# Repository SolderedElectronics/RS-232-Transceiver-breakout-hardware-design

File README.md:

# RS-232 Transceiver breakout Hardware Design

## About the Product

|  |
| :----------------------------------------------------------: |
| [Buy RS-232 Transceiver breakout](https://www.solde.red/333067) |

The RS-232 is a standard and very popular protocol for communication between two devices. It is a full-duplex protocol which means it can receive and send data at the same time, and data is sent at voltages from + 3V to + 15V for a digital “one” and from -3V to -15V for digital “zero”. This provides a more secure environment for data transmission which is resistant to noise or interference, which is why the RS-232 is often used in industry. This module converts serial communication to RS232.

---

## Repository Contents

This repository contains all design files for RS-232 Transceiver breakout, organized as follows:

- **`CAD` folder**: Contains KiCAD design files, including:
  - Schematics
  - PCB layout
  - Panel PCB layout
  - Source 3D files in Fusion360, if any
  - All files are sorted by version with a detailed change log.
- **`OUTPUTS` folder**: Includes all production-ready files, such as:
  - Bill of Materials (BOM) and interactive BOM (iBOM)
  - PDF versions of schematics
  - 3D `.step` file of the board
  - 3D-printable models
  - Gerber files for PCB manufacturing
  - Image of the pinout of the board
  - Product image
  - Compliance, legal and generic sales documents

Refer to the `Change Log` in the CAD folder for details about updates between versions.

---

## Learn More About the Product

Beyond the repository, explore the following resources:

### Soldered Verify

The **Soldered Verify** system ensures every board you purchase from Soldered is fully functional. It also provides access to exclusive test data for your product. To get started, find the unique Soldered Verify ID on your product's packaging and enter the ID on the [Soldered Verify page](https://soldered.com/verify/) to access test results and additional product details.

### Soldered Community

Soldered Community is your go-to place for technical support. Our engineers track and answer all questions posted there, and it’s a great space for the maker community. Get answers to your questions and solutions for your challenges at [Soldered Community](https://soldered.com/community).

### solde.red

solde.red is an ultimate URL shortener and information hub. Access it by typing solde.red/ followed by your product SKU, e.g., [solde.red/333000](https://solde.red/333000), to find getting-started guides, datasheets, open-source hardware and software files, certifications, images, pinouts, and more. Read more about the shortener [here](https://solde.red/info/).

---

## Contributing

Contributions are welcome! Here’s how you can get involved:

- Submit pull requests to enhance the design or fix issues.
- Report bugs or problems by opening an issue.

We encourage community collaboration to make this product even better.

---

## About Soldered

[Soldered for Makers](https://soldered.com) specializes in designing and manufacturing electronic products tailored for enthusiasts, ranging from hobbyists to professionals. Our portfolio includes electronic boards, sensors, and actuators that are widely utilized in fields such as microelectronics, mechatronics, robotics, programming, and IoT. Every product we offer is designed in-house and built upon open-source hardware and software platforms. Proudly certified and manufactured within the European Union, our catalog likely includes the product you need for your project.

We complement these products with comprehensive tutorials and manuals, product descriptions, schematics, programming codes, and project examples. Our round-the-clock [customer and technical support](https://soldered.com/community) is available for all our products, irrespective of the sales channel. Soldered’s success and services reflect our maker community’s unwavering [trust](https://www.trustpilot.com/review/soldered.com), for which we are deeply grateful. Join our community and create using Soldered products.

---

## License

All Soldered open-source hardware (OSH) is under The TAPR Open Hardware License. Read more in the LICENSE file located in this repository.

**Disclaimer:**

No warranty - all designs in this repository are distributed in the hope that they will be useful, but without any warranty. They are provided "AS IS", therefore without warranty of any kind, either expressed or implied. The entire quality and performance of what you do with the contents of this repository are your responsibility. In no event Soldered Electronics will be liable for your damages, or losses, including any general, special, incidental, or consequential damage arising out of the use or inability to use the contents of this repository. 

---

## Have fun!

Thank you for your support from your fellow makers at Soldered Electronics.

Happy Making!

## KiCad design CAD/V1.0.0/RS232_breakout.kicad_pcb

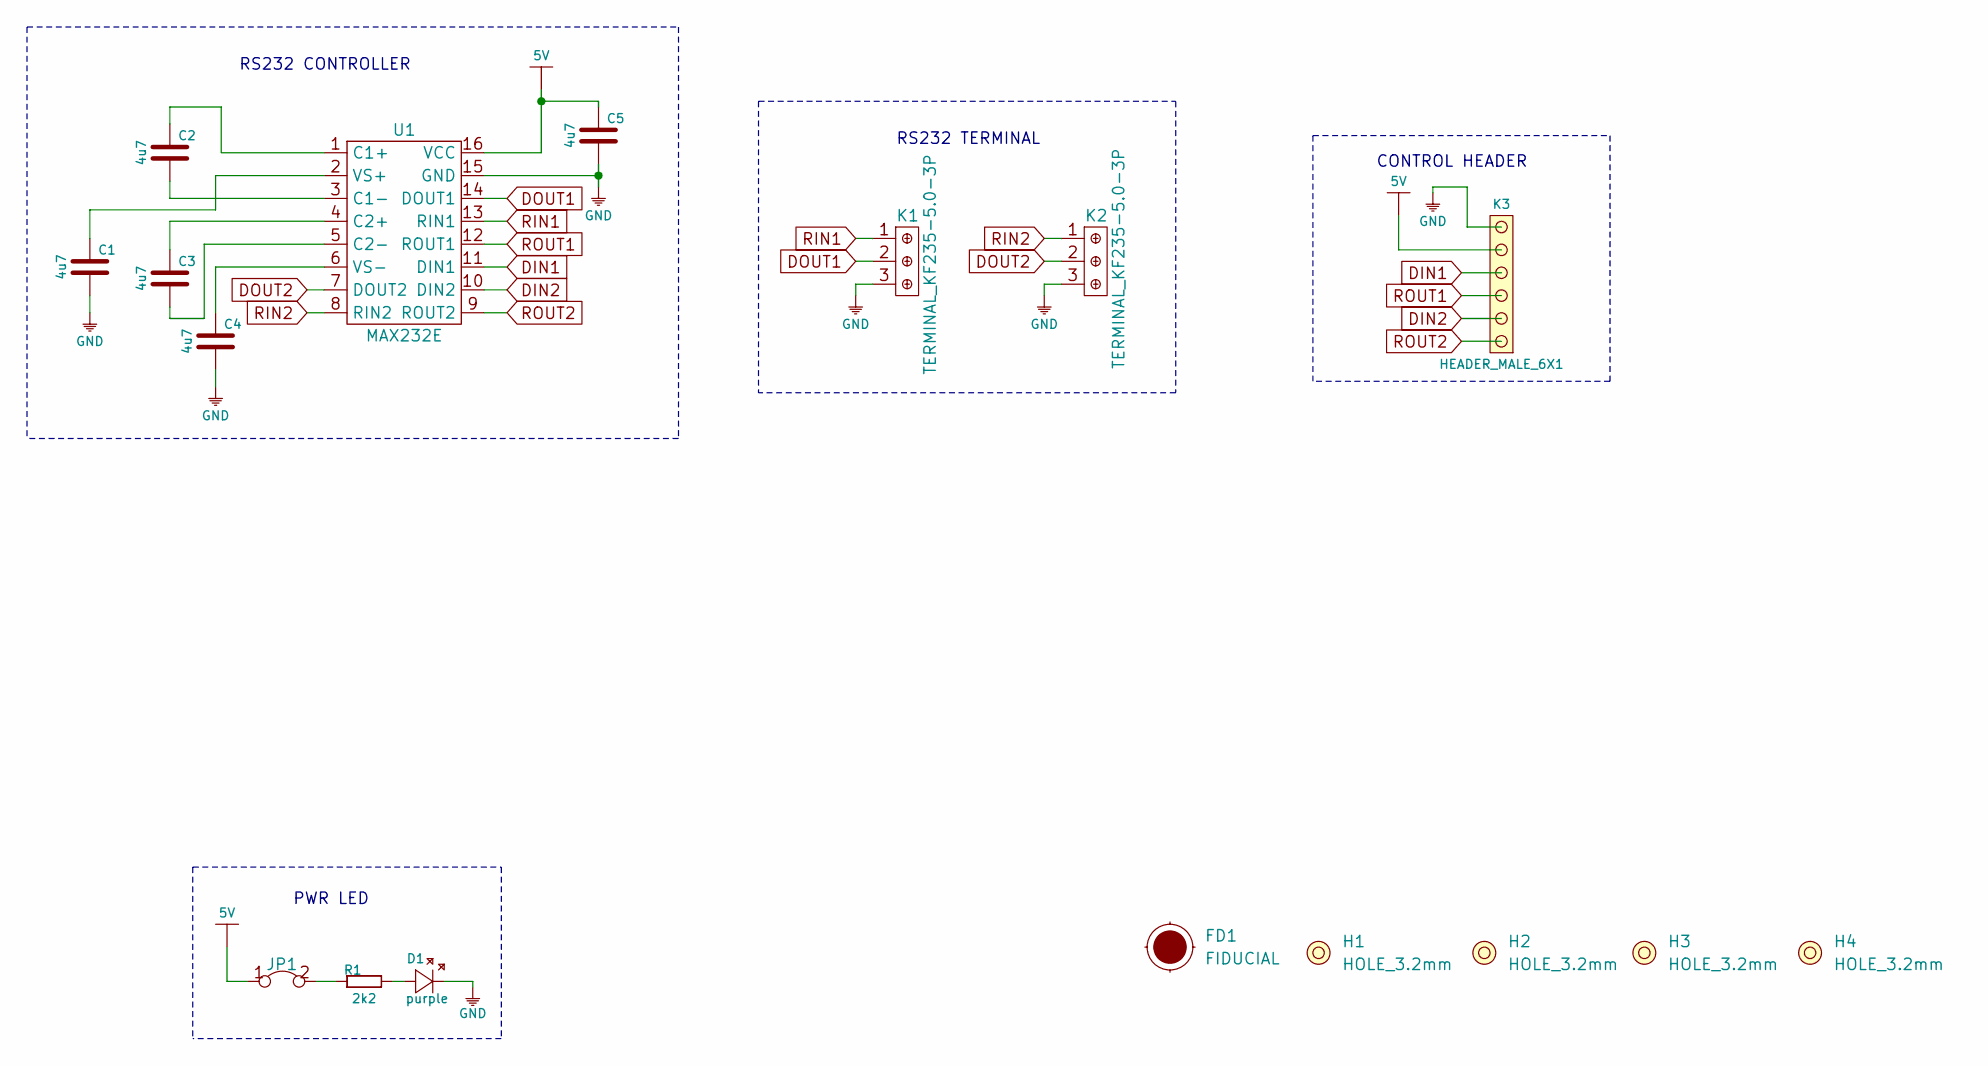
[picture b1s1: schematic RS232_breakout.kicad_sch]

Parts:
C1, C2, C3, C4, C5: 4u7; 0603C
D1: purple; 0402LED
FD1: FIDUCIAL; FIDUCIAL_23
H1, H2, H3, H4: HOLE_3.2mm
JP1: SMD-JUMPER-CONNECTED_TRACE_SLODERMASK
K1, K2: TERMINAL_KF235-5.0-3P
K3: HEADER_MALE_6X1
R1: 2k2; 0402R
U1: MAX232E; TSSOP-16

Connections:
5V: C5.2, JP1.1, K3.5, U1.16 (VCC)
DIN1: K3.4, U1.11 (DIN1)
DIN2: K3.2, U1.10 (DIN2)
DOUT1: K1.2, U1.14 (DOUT1)
DOUT2: K2.2, U1.7 (DOUT2)
GND: C1.1, C4.1, C5.1, D1.2 (K), K1.3, K2.3, K3.6, U1.15 (GND)
unnamed: C1.2, U1.2 (VS+)
unnamed: C2.1, U1.3 (C1-)
unnamed: C2.2, U1.1 (C1+)
unnamed: C3.1, U1.5 (C2-)
unnamed: C3.2, U1.4 (C2+)
unnamed: C4.2, U1.6 (VS-)
unnamed: D1.1 (A), R1.2
unnamed: JP1.2, R1.1
RIN1: K1.1, U1.13 (RIN1)
RIN2: K2.1, U1.8 (RIN2)
ROUT1: K3.3, U1.12 (ROUT1)
ROUT2: K3.1, U1.9 (ROUT2)

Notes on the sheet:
RS232 CONTROLLER
PWR LED
RS232 TERMINAL
CONTROL HEADER

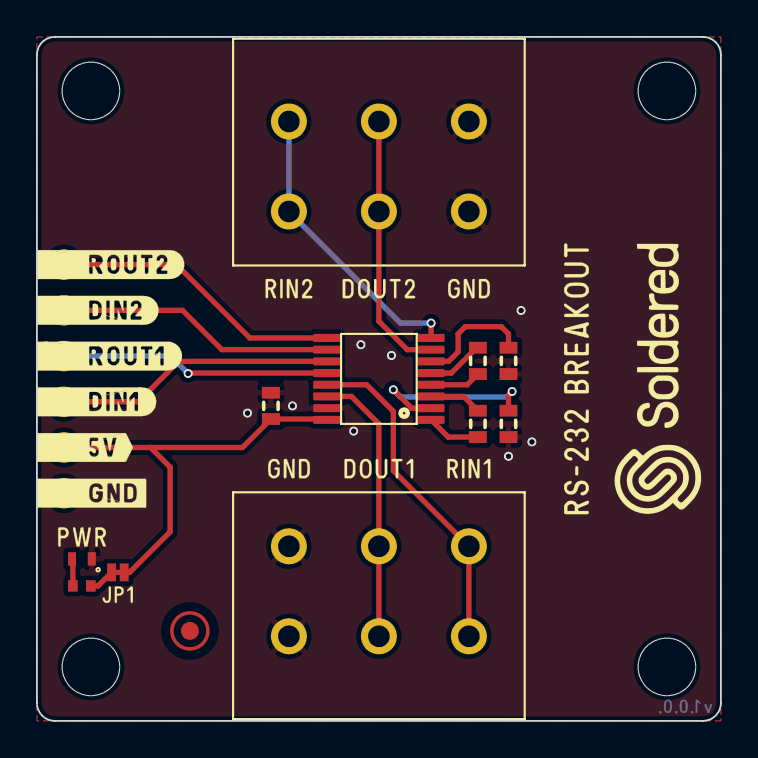
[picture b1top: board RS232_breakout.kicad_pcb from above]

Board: 2 copper layers, 38.0 x 38.0 mm, 18 parts (1 on the bottom side), 18 nets.

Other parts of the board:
Ref**: Val**; Version1.0.0.

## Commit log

2022-08-06 Updating open source files.
